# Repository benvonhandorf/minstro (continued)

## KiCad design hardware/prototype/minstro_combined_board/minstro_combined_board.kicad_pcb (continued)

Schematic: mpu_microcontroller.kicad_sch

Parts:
AE401: ANT; ANT2012LL13R2400A
C401: 10uF; C_0805_2012Metric
C402, C403, C404, C408, C411: 0.1uF; C_0603_1608Metric
C405: 1uF; C_0603_1608Metric
C406: 10nF; C_0603_1608Metric
C407: 1uF; C_0805_2012Metric
C409, C410: DNP; C_0603_1608Metric
C412, C413: 1.2pF; C_0603_1608Metric
C414, C415: 10pF; C_0603_1608Metric
D401: STATUS_LED; LED_0805_2012Metric
FB401: R_0805_2012Metric
J401: BOOT; PinHeader_1x02_P2.54mm_Vertical
J402: I2C; PinHeader_1x04_P2.54mm_Vertical
J403: USB_C_Receptacle_USB2.0_16P; USB_C_Receptacle_GCT_USB4085_PinPaste
J404: SDMMC 4b; MicroSD_Socket_Unbranded
J405: Conn_Coaxial; U.FL_Molex_MCRF_73412-0110_Vertical
JP401: SolderJumper_3_Open; Jumper_Resistor_0603_2_Way
L401: 2.4nH; L_0603_1608Metric
R401, R404: 100k; R_0603_1608Metric
R402: 100; R_0603_1608Metric
R406, R411, R412, R418: 0; R_0603_1608Metric
R407: DNP; R_0603_1608Metric
R408, R409, R410, R413, R415: 50k; R_0603_1608Metric
R414, R416: 5.1k; R_0603_1608Metric
R417: 33R; R_0603_1608Metric
R419, R420: 2.2k; R_0805_2012Metric
SW401: RST; Tac_SMD_6.4mm_Side_SPST_NO
U401: ESP32-S3; QFN-56-1EP_7x7mm_P0.4mm_EP4x4mm_ThermalVias
U402: W25Q128JVS; SOIC-8_5.3x5.3mm_P1.27mm
U403: Diode_10Pin_DFN2510A-10_10-XFDFN_SOT1176-1
Y401: 40 MHz; Crystal_SMD_2016-4Pin_2.0x1.6mm

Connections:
+3.3V: C401.1, C402.1, C403.1, C404.1, C411.2, FB401.1, J402.2, R401.1, R404.2, R407.1, R408.2, R409.1, R410.2, R413.2, R415.2, R417.1, R419.2, R420.2, U401.2 (VDD3P3), U401.3 (VDD3P3), U401.20 (VDD3P3_RTC), U401.46 (VDD3P3_CPU); also elsewhere on the board
/Audio/I2S_ADCIN: U401.14 (GPIO9); also elsewhere on the board
/Audio/I2S_ADCOUT: U401.15 (GPIO10); also elsewhere on the board
/Audio/I2S_BCLK: U401.16 (GPIO11); also elsewhere on the board
/Audio/I2S_FS: U401.17 (GPIO12); also elsewhere on the board
/Audio/I2S_MCLK: U401.13 (GPIO8); also elsewhere on the board
/Battery/PWR_CHRG: U401.39 (GPIO34); also elsewhere on the board
/Battery/PWR_GOOD: U401.40 (GPIO35); also elsewhere on the board
/Battery/Vusb: J403.A4 (VBUS), J403.A9 (VBUS), J403.B4 (VBUS), J403.B9 (VBUS); also elsewhere on the board
/Display Connectors/DISP_BL: U401.38 (GPIO33); also elsewhere on the board
/Display Connectors/DISP_CS: U401.27 (GPIO21); also elsewhere on the board
/Display Connectors/DISP_DC: U401.18 (GPIO13); also elsewhere on the board
/Display Connectors/DISP_RST: U401.24 (GPIO18); also elsewhere on the board
/Display Connectors/DISP_SCL: U401.19 (GPIO14); also elsewhere on the board
/Display Connectors/DISP_SDA: U401.23 (GPIO17); also elsewhere on the board
/Display Connectors/DISP_TS_INT: U401.21 (GPIO15/XTAL_32K_P*); also elsewhere on the board
/Display Connectors/DISP_TS_RST: U401.22 (GPIO16/XTAL_32K_N*); also elsewhere on the board
/ESP32 Microcontroller/BOOT_MODE: J401.2, U401.5 (GPIO0)
/ESP32 Microcontroller/CHIP_EN: C407.1, R404.1, SW401.2 (B), U401.4 (CHIP_PU)
/ESP32 Microcontroller/GPIO3_STRAP_PD: R401.2, U401.9 (GPIO4)
/ESP32 Microcontroller/HMI_INT: U401.42 (GPIO37); also elsewhere on the board
/ESP32 Microcontroller/HMI_WAKE: U401.41 (GPIO36); also elsewhere on the board
/ESP32 Microcontroller/RF: C412.1, L401.1, U401.1 (LNA_IN)
/ESP32 Microcontroller/RF_ANT: C413.1, JP401.2 (C), L401.2
/ESP32 Microcontroller/SD_CMD: J404.3 (CMD), R409.2, U401.47 (GPIO41/MTDI)
/ESP32 Microcontroller/SD_DAT0: J404.7 (DAT0), R408.1, U401.44 (GPIO39/MTCK)
/ESP32 Microcontroller/SD_DAT1: J404.8 (DAT1), R410.1, U401.43 (GPIO38)
/ESP32 Microcontroller/SD_DAT2: J404.1 (DAT2), R413.1, U401.49 (GPIO43/U0TXD)
/ESP32 Microcontroller/SD_DAT3: J404.2 (DAT3/CD), R415.1, U401.48 (GPIO42/MTMS)
/ESP32 Microcontroller/SD_DET: J404.10 (DET_A), U401.50 (GPIO44/U0RXD)
/ESP32 Microcontroller/SD_SCK: J404.5 (CLK), U401.45 (GPIO40/MTDO)
/ESP32 Microcontroller/SPIFLASH_CLK: R406.2, U401.33 (SPICLK)
/ESP32 Microcontroller/SPIFLASH_CS0: U401.32 (SPICS0), U402.1 (~CS)
/ESP32 Microcontroller/SPIFLASH_D: U401.35 (SPID), U402.5 (DI/IO_{0})
/ESP32 Microcontroller/SPIFLASH_HD: U401.30 (SPIHD), U402.7 (~HOLD/~RESET/IO_{3})
/ESP32 Microcontroller/SPIFLASH_Q: U401.34 (SPIQ), U402.2 (DO/IO_{1})
/ESP32 Microcontroller/SPIFLASH_WP: U401.31 (SPIWP), U402.3 (~WP/IO_{2})
/ESP32 Microcontroller/STATUS_LED: R402.2, U401.51 (GPIO45)
/ESP32 Microcontroller/USB_N: C409.1, J403.A7 (D-), J403.B7 (D-), R411.1, U403.1 (CH1)
/ESP32 Microcontroller/USB_P: C410.1, J403.A6 (D+), J403.B6 (D+), R412.1, U403.5 (CH4)
/ESP32 Microcontroller/USB_uC_N: R411.2, U401.25 (GPIO19/USB_D-)
/ESP32 Microcontroller/USB_uC_P: R412.2, U401.26 (GPIO20/USB_D+)
/ESP32 Microcontroller/VDD33A: C405.1, C406.1, FB401.2, U401.55 (VDDA), U401.56 (VDDA)
/ESP32 Microcontroller/VDD33_SPI: C408.1, R407.2, U401.29 (VDD_SPI), U402.8 (VCC)
/ESP32 Microcontroller/XTAL_N: C415.1, U401.53 (XTAL_N), Y401.3
/ESP32 Microcontroller/XTAL_P: R418.1, U401.54 (XTAL_P)
/I2C_SCL: J402.4, R420.1, U401.12 (GPIO7); also elsewhere on the board
/I2C_SDA: J402.3, R419.1, U401.11 (GPIO6); also elsewhere on the board
GND: AE401.2 (GND), C401.2, C402.2, C403.2, C404.2, C405.2, C406.2, C407.2, C408.2, C409.2, C410.2, C411.1, C412.2, C413.2, C414.2, C415.2, D401.1 (K), J401.1, J402.1, J403.A1 (GND), J403.A12 (GND), J403.B1 (GND), J403.B12 (GND), J404.6 (VSS), J404.9 (DET_B), J404.11 (SHIELD), J405.2 (Ext), R414.2, R416.2, SW401.1 (A), U401.57 (GND), U402.4 (GND), U403.3 (GND), U403.8 (GND), Y401.2, Y401.4; also elsewhere on the board
unnamed: AE401.1 (A), JP401.1 (A)
unnamed: C414.1, R418.2, Y401.1
unnamed: D401.2 (A), R402.1
unnamed: J403.A5 (CC1), R414.1
unnamed: J403.B5 (CC2), R416.1
unnamed: J404.4 (VDD), R417.2
unnamed: J405.1 (In), JP401.3 (B)
unnamed: R406.1, U402.6 (CLK)

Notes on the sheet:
Internal Pull-Ups are appropriate for desired operation on GPIO 45 and 46
3.3V Power Filtering
I2C PU Resistors
CHIP_EN RC Delay Circuit
SD Card PU Resistors
Strapping and Reset Pins
Pop only one leg of JP301
XTAL
PS Filter
Populate to power SPI from 3.3V regulator. DNP to power SPI from internal regulator. Stapping Pins & EFuses may need adjustment

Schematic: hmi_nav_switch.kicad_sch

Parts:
J801: NAV CONN; PinHeader_1x10_P2.54mm_Vertical
R801: R_2; R_0603_1608Metric
R802: R_4; R_0603_1608Metric
R803: R_1; R_0603_1608Metric
R804: R_3; R_0603_1608Metric

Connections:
/HMI Controller/NAV_A: J801.8; also elsewhere on the board
/HMI Controller/NAV_B: J801.9; also elsewhere on the board
/HMI Controller/NAV_DIR: R801.2, R802.2, R803.2, R804.2; also elsewhere on the board
/HMI Controller/NAV_SW: J801.10; also elsewhere on the board
/Nav Switch/Nav_Down_VD: J801.3, R801.1
/Nav Switch/Nav_Left_VD: J801.4, R804.1
/Nav Switch/Nav_Right_VD: J801.5, R802.1
/Nav Switch/Nav_Up_VD: J801.2, R803.1
GND: J801.1, J801.6, J801.7; also elsewhere on the board

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
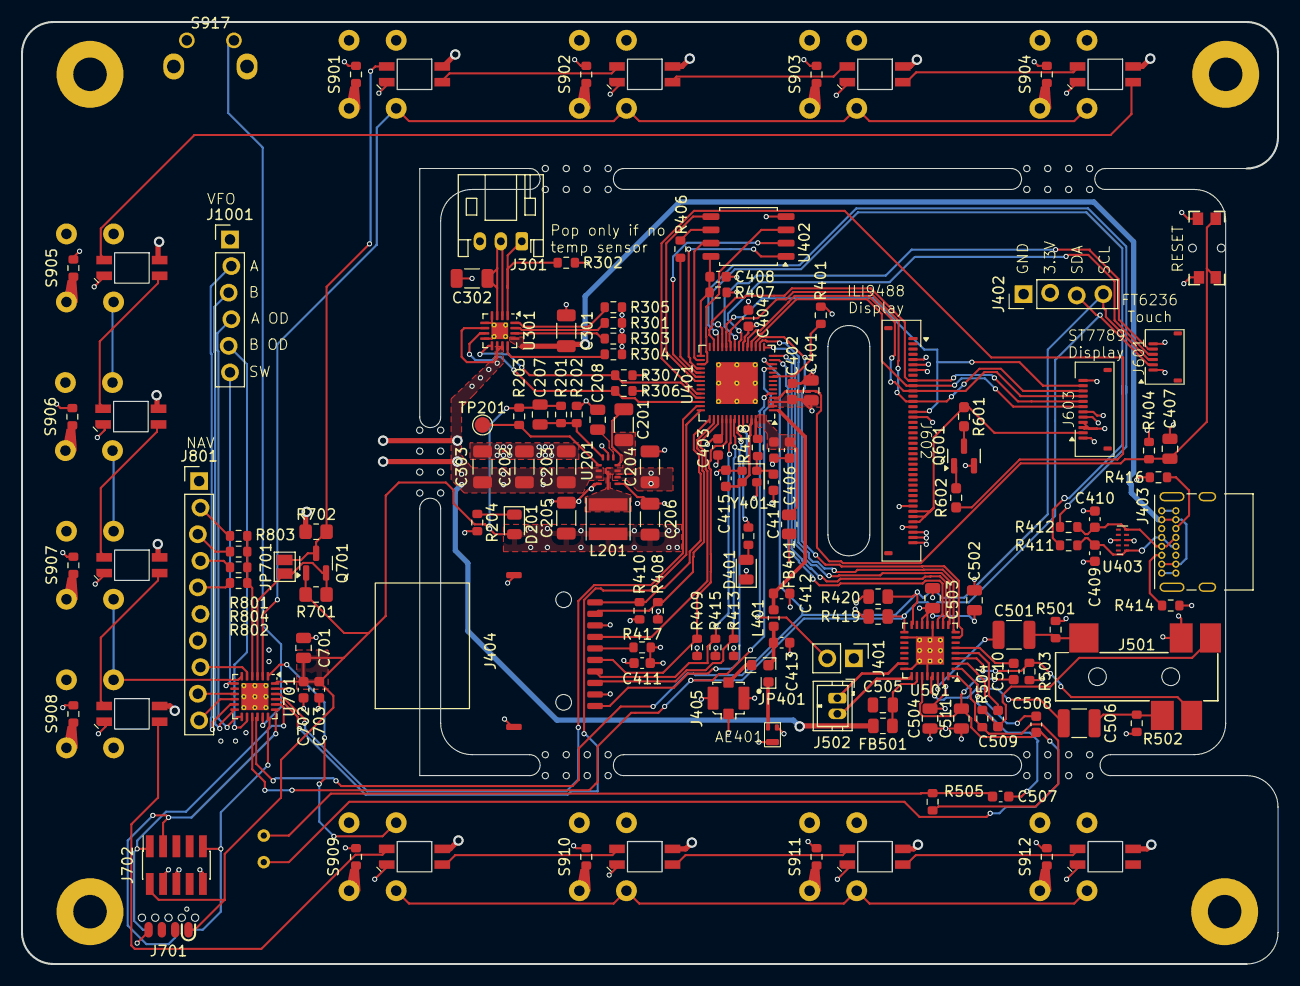
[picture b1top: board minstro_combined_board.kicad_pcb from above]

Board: 4 copper layers, 120.0 x 90.0 mm, 136 parts (1 on the bottom side), 122 nets.

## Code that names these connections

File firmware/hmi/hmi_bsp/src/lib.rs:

#![no_std]

#[cfg(feature = "rt")]
extern crate cortex_m_rt;
#[cfg(feature = "rt")]
pub use cortex_m_rt::entry;

pub use atsamd_hal as hal;
pub use hal::ehal;
pub use hal::pac;

use hal::clock::GenericClockController;
use hal::sercom::{
    Sercom1, i2c,
    uart::{self, BaudMode, Oversampling},
};
use hal::time::Hertz;

hal::bsp_pins! {
    PA02 {
        name: row_c
    }
    PA03 {
        name: row_a
    }
    PA04 {
        name: rgb_data
    }
    PA05 {
        name: nav_dir
    }
    PA06 {
        name: nav_a
    }
    PA07 {
        name: row_b
    }
    PA08 {
        /// XIN
        name: vfo_sw
    }
    PA09 {
        /// XOUT
        name: pa09
    }
    PA10 {
        name: nav_b
    }
    PA11 {
        name: nav_sw
    }
    PA14 {
        name: vfo_a
    }
    PA15 {
        name: vfo_b
    }
    PA16 {
        name: vfo_alt_a
    }
    PA17 {
        name: vfo_alt_b
    }
    PA22 {
        name: sda
        aliases: {
            AlternateC: Sda
        }
    }
    PA23 {
        name: scl
        aliases: {
            AlternateC: Scl
        }
    }
    PA24 {
        name: int
    }
    PA25 {
        name: pa25
    }
    PA27 {
        /// RST pin
        name: power_sw
    }
    PA28 {
        /// RST pin
        name: pa28
    }
    PA30 {
        /// SWCLK
        name: pa30
    }
    PA31 {
        /// SWDIO
        name: pa31
    }
}

//pub type UartPads = uart::Pads<Sercom0, UartRx, UartTx>;

/// UART device for the labelled RX & TX pins
//pub type Uart = uart::Uart<uart::Config<UartPads>, uart::Duplex>;

/// Convenience for setting up the D1 and D14 pins to
/// operate as UART RX/TX (respectively) running at the specified baud.
// pub fn uart(
//     clocks: &mut GenericClockController,
//     baud: impl Into<Hertz>,
//     sercom0: pac::SERCOM0,
//     pm: &mut pac::PM,
//     rx: impl Into<UartRx>,
//     tx: impl Into<UartTx>,
// ) -> Uart {
//     let gclk0 = clocks.gclk0();
//     let clock = &clocks.sercom0_core(&gclk0).unwrap();
//     let baud = baud.into();
//     let pads = uart::Pads::default().rx(rx.into()).tx(tx.into());
//     uart::Config::new(pm, sercom0, pads, clock.freq())
//         .baud(baud, BaudMode::Fractional(Oversampling::Bits16))
//         .enable()
// }

/// I2C pads for the labelled I2C peripheral
///
/// You can use these pads with other, user-defined [`i2c::Config`]urations.
pub type I2cPads = i2c::Pads<Sercom1, Sda, Scl>;

/// I2C master for the labelled I2C peripheral
///
/// This type implements [`Read`](ehal::blocking::i2c::Read),
/// [`Write`](ehal::blocking::i2c::Write) and
/// [`WriteRead`](ehal::blocking::i2c::WriteRead).
pub type I2c = i2c::I2c<i2c::Config<I2cPads>>;

/// Convenience for setting up the labelled SDA, SCL pins to
/// operate as an I2C master running at the specified frequency.
pub fn i2c_master(
    clocks: &mut GenericClockController,
    baud: impl Into<Hertz>,
    sercom: pac::SERCOM1,
    pm: &mut pac::PM,
    sda: impl Into<Sda>,
    scl: impl Into<Scl>,
) -> I2c {
    let gclk0 = clocks.gclk0();
    let clock = &clocks.sercom0_core(&gclk0).unwrap();
    let freq = clock.freq();
    let baud = baud.into();
    let pads = i2c::Pads::new(sda.into(), scl.into());
    i2c::Config::new(pm, sercom, pads, freq).baud(baud).enable()
}

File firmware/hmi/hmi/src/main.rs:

#![no_std]
#![no_main]

mod comms;
mod encoder;
mod i2c_peripheral;
mod protocol;

use core::borrow::Borrow;

use hmi_bsp::ehal;
use hmi_bsp::pac::gclk;
use hmi_bsp as bsp;

use bsp::entry;
use bsp::hal;
use bsp::pac;

use hal::sercom::Sercom1;
use hal::time::MegaHertz;
use hal::timer::TimerCounter;

#[cfg(not(feature = "use_semihosting"))]
use panic_halt as _;
#[cfg(feature = "use_semihosting")]
use panic_semihosting as _;

use cortex_m::peripheral::NVIC;
use pac::{interrupt, CorePeripherals, Peripherals};
use cortex_m::interrupt as interrupt_helpers;

use hal::clock::GenericClockController;
use hal::delay::Delay;
use hal::ehal::blocking::delay::DelayMs;
use hal::prelude::*;
use hal::sercom::Sercom;
use hal::sercom::i2c;

use hal::gpio::{
    Pin,
    AlternateB,
};

use hal::adc::{
    Adc,
    SampleRate,
    Gain,
    Resolution,
};

use hal::time::*;
use hal::timer::*;

use smart_leds::{hsv::RGB8, SmartLedsWrite};
use ws2812_timer_delay::Ws2812;

use rtt_target::{rtt_init_print, rprintln};

const ADDRESS: u8 = 0x22;

#[entry]
fn main() -> ! {
    //Initial hardware configuration
    let mut peripherals = Peripherals::take().unwrap();
    let mut core = CorePeripherals::take().unwrap();
    let mut clocks = GenericClockController::with_internal_32kosc(
        peripherals.GCLK,
        &mut peripherals.PM,
        &mut peripherals.SYSCTRL,
        &mut peripherals.NVMCTRL,
    );

    let gclk0 = clocks.gclk0();

    let mut delay = Delay::new(core.SYST, &mut clocks);

    rtt_init_print!();

    let mut adc = Adc::adc(peripherals.ADC, &mut peripherals.PM, &mut clocks);
    adc.samples(SampleRate::_128);
    adc.resolution(Resolution::_12BIT);

    let pins = bsp::Pins::new(peripherals.PORT);

    //Configure I2C
    // let sercom1_clock = &clocks.sercom1_core(&gclk0).unwrap();
    // let pads: i2c::Pads<
    //     Sercom1,
    //     hal::gpio::Pin<hal::gpio::PA22, _>,
    //     hal::gpio::Pin<hal::gpio::PA23, _>,
    // > = i2c::Pads::new(pins.sda, pins.scl);

    // let mut sercom = peripherals.SERCOM1;

    // sercom.enable_apb_clock(&peripherals.PM);

    unsafe {
        core.NVIC.set_priority(interrupt::SERCOM0, 1);
        NVIC::unmask(interrupt::SERCOM0);
    }

    let interrupt_pin = Some(pins.int.into_push_pull_output());

    // i2c_peripheral::configure_bus_status();

    // i2c_peripheral::configure_sercom(sercom, ADDRESS);
    pins.scl.into_floating_input();
    pins.sda.into_floating_input();

    let mut power_sw = pins.power_sw.into_pull_up_input();

    let mut row_a: Pin<_, AlternateB> = pins.row_a.into_mode();
    let mut row_b: Pin<_, AlternateB> = pins.row_b.into_mode();
    let mut row_c: Pin<_, AlternateB> = pins.row_c.into_mode();
    let mut nav_dir: Pin<_, AlternateB> = pins.nav_dir.into_mode();

    let nav_a = pins.nav_a.into_pull_up_input();

    let tc12_led_timer = &clocks.tc1_tc2(&gclk0).unwrap();

    let mut led_timer = TimerCounter::tc1_(tc12_led_timer, peripherals.TC1, &mut peripherals.PM);
    led_timer.start(MegaHertz::MHz(7).into_duration()); //TODO: This was 7 in the other project.  Investigate, docs call for 3

    let mut led_data_pin = pins.rgb_data.into_push_pull_output();
    led_data_pin.set_drive_strength(true);

    let mut led_strand = Ws2812::new(led_timer, led_data_pin);

    let mut led_data: [RGB8; 12] = [RGB8::default() ;12];

    led_strand.write(led_data.iter().cloned())
            .unwrap();

    let mut cycle = 0;

    let mut reading_a : u16;
    let mut reading_b : u16;
    let mut reading_c : u16;
    let mut reading_dir : u16;
    let mut power_state : bool = false;

    loop {
        //Process protocol commands
        // let command = interrupt_helpers::free(|cs| {
        //     if let Some(comms_status) = i2c_peripheral::BUS_STATUS.borrow(cs).borrow_mut().as_mut()
        //     {
        //         comms_status.process()
        //     } else {
        //         None
        //     }
        // });

        for pixel in &mut led_data {
            pixel.r = 0;
            pixel.g = 0;
            pixel.b = 0;
        }

        // led_data[cycle].g = 20;

        led_strand.write(led_data.iter().cloned())
            .unwrap();

        cycle = (cycle + 1) % 12;

        reading_a = adc.read(&mut row_a).unwrap();
        reading_b = adc.read(&mut row_b).unwrap();
        reading_c = adc.read(&mut row_c).unwrap();
        reading_dir = adc.read(&mut nav_dir).unwrap();

        power_state = power_sw.is_low().unwrap();

        rprintln!("{} {}, {}, {}, {}", power_state, reading_a, reading_b, reading_c, reading_dir);

    }
}

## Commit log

2025-05-20 Initial HMI board schematic work
2025-05-20 Remove lockfiles
2025-05-20 Added column jumpers
2025-05-24 Add display board
2025-06-02 Combined board started
2025-06-05 Combined board started layout
2025-06-06 Schematic ERC complete
2025-06-06 Footprint assignment and PCB layout work
2025-06-08 Layout WIP
2025-06-08 Remove locks
2025-06-09 Layout and routing Power and initial signals, SD card
2025-06-10 Routing mostly completed
2025-06-11 PCB size fix started
2025-06-12 Board resizing
2025-06-12 Layout completed, initial review
2025-06-12 Move slot and begin re-layout
2025-06-13 Adjust connector positions, thicken Vusb traces, move onboard microphone, improve silkscreen
2025-06-23 Firmware started
2025-06-24 HMI processor firmware started
2025-06-26 Bringup WIP. I2C enumerating.
2025-06-28 Improvements in SD card bring up test, board and mode defines in code for easier iteration.
